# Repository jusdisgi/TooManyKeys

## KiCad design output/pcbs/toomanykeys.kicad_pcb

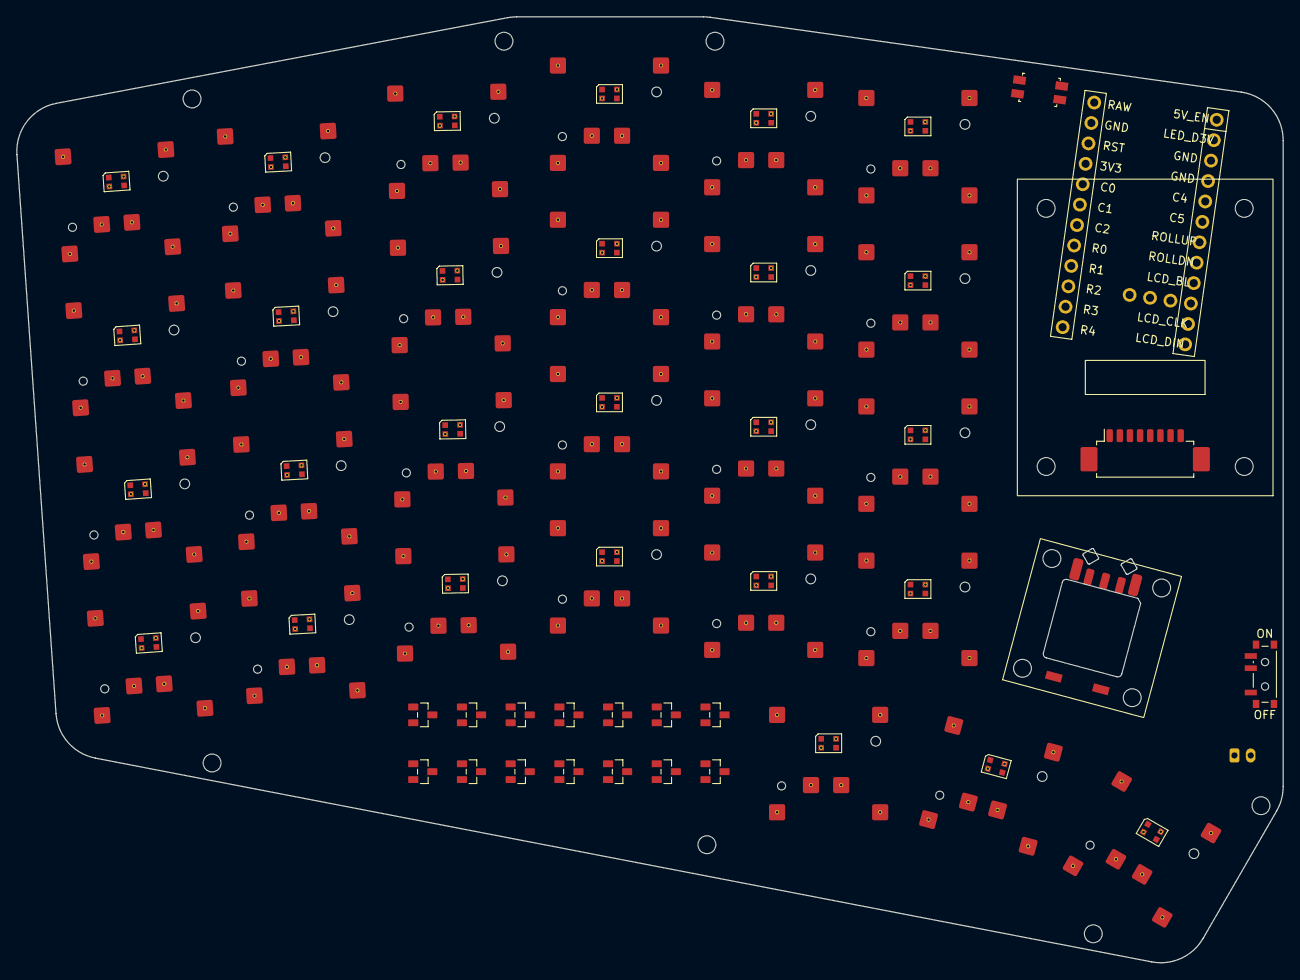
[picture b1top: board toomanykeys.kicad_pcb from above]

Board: 2 copper layers, 156.0 x 116.5 mm, 82 parts (1 on the bottom side), 79 nets, no tracks yet.

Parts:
CONN1: Molex_PicoBlade_53261-0871_1x08-1MP_P1.25mm_Horizontal
D1, D2, D3, D4, D5, D6, D7, D8, D9, D10, D11, D12, D13, D14: BAV70; BAV70 SOT23
JST1: battery_connector_jst_ph_2
LCD1: LCD_1.69_Waveshare
LED1, LED2, LED3, LED4, LED5, LED6, LED7, LED8, LED9, LED10, LED11, LED12, LED13, LED14, LED15, LED16, LED17, LED18, LED19, LED20, LED21, LED22, LED23, LED24, LED25, LED26, LED27: LED_WS2812B-2020_PLCC4_2.0x2.0mm
MCU1: mcu_nice_nano
MH1, MH2, MH3, MH4, MH5, MH6, MH7: mounting_hole_npth
PWR1: power_switch_smd_side
RE1: CKW12
RST1: reset_switch_smd_side
S1, S2, S3, S4, S5, S6, S7, S8, S9, S10, S11, S12, S13, S14, S15, S16, S17, S18, S19, S20, S21, S22, S23, S24, S25, S26, S27: PG1316S

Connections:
3V3: CONN1.1, MCU1.21
5V: LED1.2, LED2.2, LED3.2, LED4.2, LED5.2, LED6.2, LED7.2, LED8.2, LED9.2, LED10.2, LED11.2, LED12.2, LED13.2, LED14.2, LED15.2, LED16.2, LED17.2, LED18.2, LED19.2, LED20.2, LED21.2, LED22.2, LED23.2, LED24.2, LED25.2, LED26.2, LED27.2
BAT_P: JST1.2, PWR1.2
C0: MCU1.20, S1.1, S2.1, S3.1, S4.1
C1: MCU1.19, S5.1, S6.1, S7.1, S8.1
C2: MCU1.18, S9.1, S10.1, S11.1, S12.1, S25.1
C3: MCU1.27, S13.1, S14.1, S15.1, S16.1, S26.1
C4: MCU1.5, S17.1, S18.1, S19.1, S20.1, S27.1
C5: MCU1.6, RE1.S1, S21.1, S22.1, S23.1, S24.1
GND: CONN1.2, JST1.1, LED1.4, LED2.4, LED3.4, LED4.4, LED5.4, LED6.4, LED7.4, LED8.4, LED9.4, LED10.4, LED11.4, LED12.4, LED13.4, LED14.4, LED15.4, LED16.4, LED17.4, LED18.4, LED19.4, LED20.4, LED21.4, LED22.4, LED23.4, LED24.4, LED25.4, LED26.4, LED27.4, MCU1.3, MCU1.4, MCU1.23, RE1.B, RST1.1, RST1.3, S1.3, S2.3, S3.3, S4.3, S5.3, S6.3, S7.3, S8.3, S9.3, S10.3, S11.3, S12.3, S13.3, S14.3, S15.3, S16.3, S17.3, S18.3, S19.3, S20.3, S21.3, S22.3, S23.3, S24.3, S25.3, S26.3, S27.3
LCD_BL: CONN1.8, MCU1.9
LCD_CLK: CONN1.4, MCU1.11
LCD_CS: CONN1.5, MCU1.26
LCD_DC: CONN1.6, MCU1.10
LCD_DIN: CONN1.3, MCU1.12
LCD_RST: CONN1.7, MCU1.25
LED_1: LED26.1, LED27.3
LED_2: LED25.1, LED26.3
LED_3: LED21.1, LED25.3
LED_4: LED21.3, LED22.1
LED_5: LED22.3, LED23.1
LED_6: LED23.3, LED24.1
LED_7: LED20.1, LED24.3
LED_8: LED19.1, LED20.3
LED_9: LED18.1, LED19.3
LED_10: LED17.1, LED18.3
LED_11: LED13.1, LED17.3
LED_12: LED13.3, LED14.1
LED_13: LED14.3, LED15.1
LED_14: LED15.3, LED16.1
LED_15: LED12.1, LED16.3
LED_16: LED11.1, LED12.3
LED_17: LED10.1, LED11.3
LED_18: LED9.1, LED10.3
LED_19: LED5.1, LED9.3
LED_20: LED5.3, LED6.1
LED_21: LED6.3, LED7.1
LED_22: LED7.3, LED8.1
LED_23: LED4.1, LED8.3
LED_24: LED3.1, LED4.3
LED_25: LED2.1, LED3.3
LED_26: LED1.1, LED2.3
R0: D1.3, D2.3, D3.3, MCU1.17
R1: D4.3, D5.3, D6.3, MCU1.16
R2: D7.3, D8.3, D9.3, MCU1.15
R3: D10.3, D11.3, D12.3, MCU1.14
R4: D13.3, D14.3, MCU1.13
RAW: MCU1.24, PWR1.3
ROLLDN: MCU1.8, RE1.C
ROLLUP: MCU1.7, RE1.A
RST: MCU1.22, RST1.2, RST1.4
finger_index_bottom: D12.1, S17.2
finger_index_home: D9.1, S18.2
finger_index_num: D3.1, S20.2
finger_index_top: D6.1, S19.2
finger_inner_bottom: D12.2, S21.2
finger_inner_home: D9.2, S22.2
finger_inner_num: D3.2, S24.2
finger_inner_top: D6.2, S23.2
finger_middle_bottom: D11.1, S13.2
finger_middle_home: D8.2, S14.2
finger_middle_num: D2.2, S16.2
finger_middle_top: D5.2, S15.2
finger_outer_bottom: D10.2, S1.2
finger_outer_home: D7.2, S2.2
finger_outer_num: D1.2, S4.2
finger_outer_top: D4.2, S3.2
finger_pinky_bottom: D10.1, S5.2
finger_pinky_home: D7.1, S6.2
finger_pinky_num: D1.1, S8.2
finger_pinky_top: D4.1, S7.2
finger_ring_bottom: D11.2, S9.2
finger_ring_home: D8.1, S10.2
finger_ring_num: D2.1, S12.2
finger_ring_top: D5.1, S11.2
roller: D13.1, RE1.S2
thumb_far_fan: D14.2, S27.2
thumb_mid_fan: D14.1, S26.2
thumb_near_fan: D13.2, S25.2
